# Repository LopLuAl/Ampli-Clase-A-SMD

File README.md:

# Ampli-Clase-A-SMD
Amplificador realizado con Kicad y componentes de montaje superficial

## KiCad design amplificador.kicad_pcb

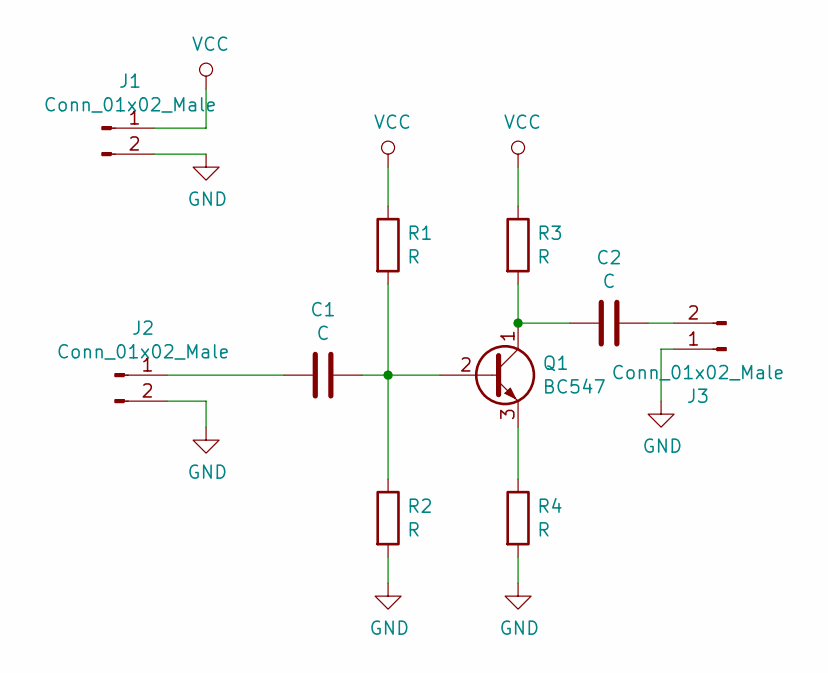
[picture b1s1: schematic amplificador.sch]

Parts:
C1, C2: C; R_0805_2012Metric_Pad1.15x1.40mm_HandSolder
J1, J2, J3: Conn_01x02_Male; PinHeader_1x02_P1.00mm_Vertical
Q1: BC547; SOT-323_SC-70_Handsoldering
R1, R2, R3, R4: R; R_0805_2012Metric_Pad1.15x1.40mm_HandSolder

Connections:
GND: J1.2, J2.2, J3.1, R2.2, R4.2
unnamed: C1.1, Q1.2 (B), R1.2, R2.1
unnamed: C1.2, J2.1
unnamed: C2.1, J3.2
unnamed: C2.2, Q1.1 (C), R3.2
unnamed: Q1.3 (E), R4.1
VCC: J1.1, R1.1, R3.1

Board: 2 copper layers, 10 parts (0 on the bottom side), 7 nets, no tracks yet.

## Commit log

2021-03-10 Commit 0
    Ejemplo de prueba
